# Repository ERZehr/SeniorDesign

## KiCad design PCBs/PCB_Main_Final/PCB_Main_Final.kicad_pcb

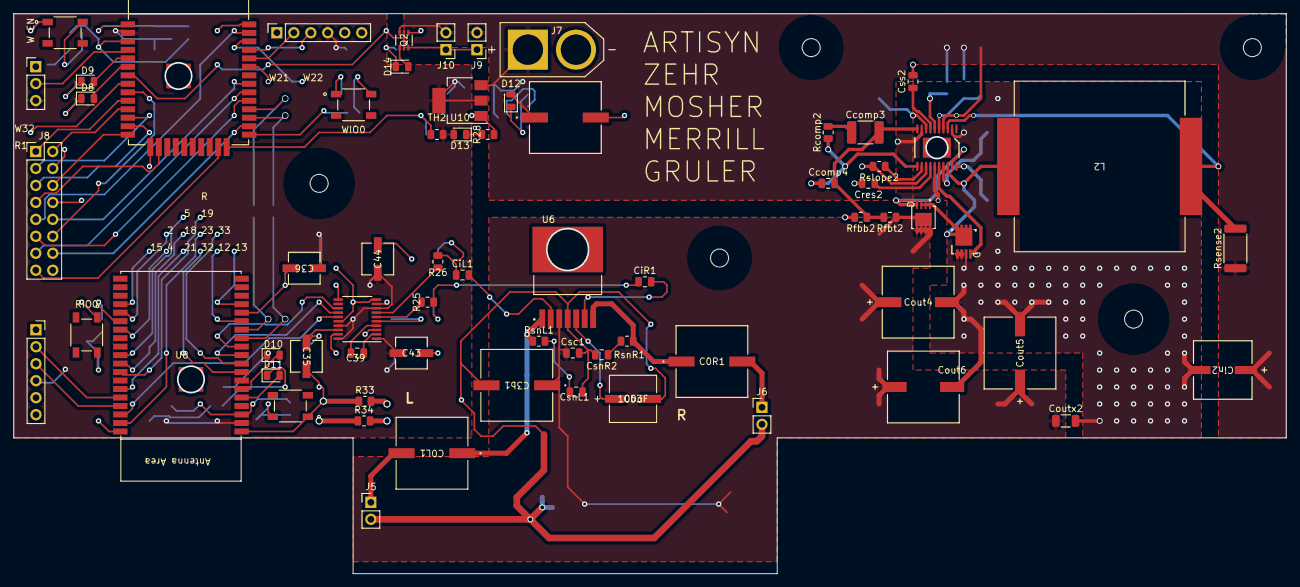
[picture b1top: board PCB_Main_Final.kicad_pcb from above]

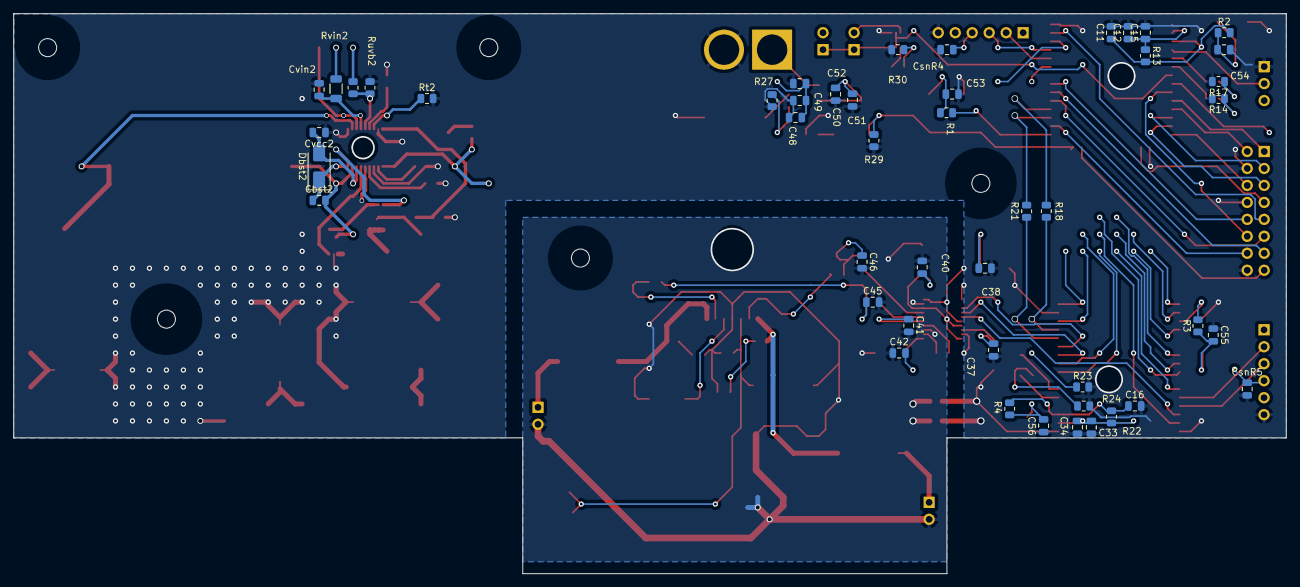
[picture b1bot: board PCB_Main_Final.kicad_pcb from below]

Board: 2 copper layers, 190.5 x 83.8 mm, 119 parts (47 on the bottom side), 85 nets.

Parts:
Boot2ROVER2, Boot2WROOM2: PinSocket_1x06_P2.54mm_Vertical
C0L1, C0R1, C3b1, C47: 1000uF; Audio_1000uF
C11, C15, C16, C34, C48, C49, C51, C53, C54, C55, C56: .1uF; C_0805_2012Metric
C12, C33: 22uF; C_0805_2012Metric
C35, C36, C43, C44: 10uF; EX_DAC_ELEC_CAPS_10uF
C37, C38, C40, C42: 0.1uF; C_0805_2012Metric
C39, C41: 2.2uF; C_0805_2012Metric
C45, C46: 2.2nF; C_0805_2012Metric
C50, C52: 10uF; C_0805_2012Metric
Cb3: 100uF; Audio_100uF
Cbst2: 470.0 nF; C_0805_2012Metric
Ccomp3: 18.0 nF; C_1812_4532Metric
Ccomp4: 1.0 nF; C_0805_2012Metric
CiL1: .1uF; C_0805_2012Metric
CiR1: .1uF; C_0805_2012Metric
Cin2: 270uF; PCAP_SVP_E7_PAN
Cout4, Cout5, Cout6: 560.0 uF; PCAP_SVP_F12_PAN
Coutx2: 47.0 uF; C_1206_3216Metric
Cres2: 470.0 nF; C_0805_2012Metric
Csc1: .1uF; C_0805_2012Metric
CsnL1: .1uF; C_0805_2012Metric
CsnR2, CsnR4, CsnR5: .1uF; C_0805_2012Metric
Css2: 33.0 nF; C_0805_2012Metric
Cvcc2: 10.0 uF; C_0805_2012Metric
Cvin2: 470.0 nF; C_0805_2012Metric
D8, D9, D10, D11: LED; LED_0805_2012Metric
D12, D13, D14: RED LED; LED_0805_2012Metric
Dbst2: D_Schottky; D_SMA
H6, H7, H8, H9, H10: MountingHole; MountingHole_2.7mm
J5: To_Speaker_L; PinHeader_1x02_P2.54mm_Vertical
J6: To_Speaker_R; PinHeader_1x02_P2.54mm_Vertical
J7: XT60-M; AMASS_XT60-M
J8: HUB75; PinHeader_2x08_P2.54mm_Vertical
J9, J10: fan connector; PinHeader_1x02_P2.54mm_Vertical
L2: 3.3 µH; IND_R3-R_EAT
LightSensorConnector2: Conn_01x03_Pin; PinHeader_1x03_P2.54mm_Vertical
M3: CSD17581Q3; CSD17309Q3
M4: CSD17581Q3A
Q2: Fan_NMOS; Fan_MOSFET
R1, R2, R3, R4: 100; R_0805_2012Metric
R13, R22, R29: 10k; R_0805_2012Metric
R14, R17, R23, R24, R28, R30: 1k; R_0805_2012Metric
R18, R21, R33, R34: 0; R_0805_2012Metric
R25, R26: 470; R_0805_2012Metric
R27: 2k; R_0805_2012Metric
RIO0: SW_Push; Boot_Switches
Rcomp2: 23.7k; R_0805_2012Metric
Rfbb2: 3.65k; R_0805_2012Metric
Rfbt2: 39.0k; R_0805_2012Metric
Rsense2: 1.5m; R_2512_6332Metric
Rslope2: 150.0k; R_0805_2012Metric
RsnL1: 2.7; R_0805_2012Metric
RsnR1: 2.7; R_0805_2012Metric
Rt2: 41.2k; R_0805_2012Metric
Ruvb2: 19.1k; R_0805_2012Metric
Ruvt2: 49.9k; R_0805_2012Metric
Rvin2: 3.01; R_1206_3216Metric
SW8: SW_Push; Boot_Switches
TH2: Thermistor; R_0805_2012Metric
U6: LM4752TS; LM4752
U7: ESP32-WROOM-E; ESP32-WROOM-32E
U8: ESP32-WROVER-E
U9: PCM5102A; TSSOP-20_4.4x6.5mm_P0.65mm
U10: AMS1117-3.3; SOT-223-3_TabPin2
U11: LM5122MH/NOPB; LM512220A_L
W EN: SW_Push; Boot_Switches
WIO0: SW_Push; Boot_Switches

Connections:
3.3V: Boot2ROVER2.4 (VCC), Boot2WROOM2.4 (VCC), C12.1, C15.1, C33.1, C34.1, C36.1, C38.2, C40.2, C42.2, C43.1, C44.1, C51.1, C52.1, CsnR4.1, CsnR5.1, D13.2 (A), LightSensorConnector2.3, R13.1, R22.1, TH2.1, U7.2 (3V3), U8.2 (3V3), U9.1 (CPVDD), U9.8 (AVDD), U9.17 (XSMT), U9.20 (DVDD), U10.2 (VO)
5V: C47.1, C48.1, C49.1, C50.1, Cin2.1, D12.2 (A), J7.P (POS), J9.2, J10.2, Q2.6 (D1), Rsense2.1, Ruvt2.1, Rvin2.1, U10.3 (VI), U11.4 (CSP)
14V: C3b1.1, Cout4.1, Cout5.1, Cout6.1, Coutx2.1, Csc1.1, M4.5 (DRAIN), M4.6 (DRAIN), M4.7 (DRAIN), M4.8 (DRAIN), M4.9 (DRAIN), Rfbt2.1, U6.3 (Vcc)
AGND: C3b1.2, C40.1, C41.2, C42.1, C43.2, C44.2, C45.2, C46.2, Cb3.2, Csc1.2, CsnL1.2, CsnR2.2, J5.2, J6.2, R33.2, R34.2, U6.4 (GND), U9.3 (CPGND), U9.9 (AGND)
A_PIN: J8.9, U7.37 (GPIO23)
B1_PIN: J8.3, U7.12 (ADC2_CH7/GPIO27)
B2_PIN: J8.7, U7.16 (MTCK/GPIO13/ADC2_CH4)
B_PIN: J8.10, U7.31 (GPIO19)
CLK_PIN: J8.13, U7.30 (GPIO18)
C_PIN: J8.11, U7.29 (GPIO5)
D_PIN: J8.12, U7.9 (32K_XN/GPIO33/ADC1_CH5)
EN_ROVER: C16.1, R4.2, R22.2, U8.3 (EN/CHIP_PU)
EN_WROOM: C11.1, R2.2, R13.2, U7.3 (EN/CHIP_PU)
G1_PIN: J8.2, U7.11 (DAC_2/ADC2_CH9/GPIO26)
G2_PIN: J8.6, U7.14 (MTDI/GPIO12/ADC2_CH5)
GND: Boot2ROVER2.6 (GND), Boot2WROOM2.6 (GND), C11.2, C12.2, C15.2, C16.2, C33.2, C34.2, C35.2, C36.2, C37.2, C38.1, C47.2, C48.2, C49.2, C50.2, C51.2, C52.2, C53.1, C54.1, C55.1, C56.1, Cin2.2, Cout4.2, Cout5.2, Cout6.2, Coutx2.2, Cres2.2, CsnR4.2, CsnR5.2, Css2.2, Cvcc2.1, Cvin2.2, J7.N (NEG), J8.4, J8.8, J8.16, LightSensorConnector2.1, M3.1 (S1), M3.2 (S2), M3.3 (S3), Q2.4 (S2), R14.2, R17.2, R23.2, R24.2, R27.2, R28.2, R29.2, R30.2, R33.1, R34.1, RIO0.1, Rfbb2.2, Rslope2.2, Rt2.2, Ruvb2.2, SW8.1, U7.1 (GND), U7.15 (GND), U7.38 (GND), U7.39 (GND_THERMAL), U8.1 (GND), U8.15 (GND), U8.38 (GND), U8.39 (GND_THERMAL), U9.10 (DEMP), U9.11 (FLT), U9.16 (FMT), U9.19 (DGND), U10.1 (GND), U11.2 (OPT), U11.9 (AGND), U11.13 (MODE), U11.15 (PGND), W EN.1, WIO0.1
I2S-BCK: U8.11 (DAC_2/ADC2_CH9/GPIO26), U9.13 (BCK)
I2S-WS: U8.36 (GPIO22), U9.15 (LRCK)
I2S_DATA: U8.10 (DAC_1/ADC2_CH8/GPIO25), U9.14 (DIN)
IO0_ROVER: R3.2, U8.25 (GPIO0/BOOT/ADC2_CH1)
IO0_WROOM: R1.2, U7.25 (GPIO0/BOOT/ADC2_CH1)
Left_Audio: C46.1, CiL1.1, R26.2
Light_Reading: LightSensorConnector2.2, U7.4 (SENSOR_VP/GPIO36/ADC1_CH0)
unnamed: C53.2, R1.1, WIO0.2
unnamed: C54.2, R2.1, W EN.2
unnamed: C55.2, R3.1, RIO0.2
unnamed: C56.2, R4.1, SW8.2
unnamed: Ccomp3.1, Rcomp2.2
unnamed: CsnL1.1, RsnL1.2
unnamed: CsnR2.1, RsnR1.2
unnamed: D8.2 (A), U7.6 (GPIO34/ADC1_CH6)
unnamed: D8.1 (K), R14.1
unnamed: D9.2 (A), U7.5 (SENSOR_VN/GPIO39/ADC1_CH3)
unnamed: D9.1 (K), R17.1
unnamed: D10.2 (A), U8.6 (GPIO34/ADC1_CH6)
unnamed: D10.1 (K), R23.1
unnamed: D11.2 (A), U8.5 (SENSOR_VN/GPIO39/ADC1_CH3)
unnamed: D11.1 (K), R24.1
unnamed: D12.1 (K), R27.1
unnamed: D13.1 (K), R28.1
unnamed: D14.2 (A), Q2.1 (S1)
unnamed: D14.1 (K), R30.1
unnamed: Cvcc2.2, Dbst2.2 (A), U11.17 (VCC)
unnamed: Cbst2.1, Dbst2.1 (K), U11.20 (BST)
unnamed: J9.1, J10.1, Q2.3 (D2)
unnamed: C0L1.2, J5.1
unnamed: C0R1.2, J6.1
unnamed: Cbst2.2, L2.2, M3.5 (D1), M3.6 (D2), M3.7 (D3), M3.8 (D4), M3.9 (Back), M4.1 (SOURCE), M4.2 (SOURCE), M4.3 (SOURCE), U11.18 (SW)
unnamed: M3.4 (G), U11.16 (LO)
unnamed: M4.4 (GATE), U11.19 (HO)
unnamed: C39.2, U9.4 (CAPM)
unnamed: C39.1, U9.2 (CAPP)
unnamed: C35.1, C37.1, U9.18 (LDOO)
unnamed: R25.1, U9.6 (OUTL)
unnamed: R26.1, U9.7 (OUTR)
unnamed: C41.1, U9.5 (VNEG)
unnamed: Ccomp4.1, Rcomp2.1, U11.11 (COMP)
unnamed: L2.1, Rsense2.2, U11.3 (CSN)
unnamed: Ccomp3.2, Ccomp4.2, Rfbb2.1, Rfbt2.2, U11.10 (FB)
unnamed: Cres2.1, U11.14 (RES)
unnamed: Rslope2.1, U11.12 (SLOPE)
unnamed: Css2.1, U11.7 (SS)
unnamed: Rt2.1, U11.8 (SYNCIN_RT)
unnamed: Ruvb2.1, Ruvt2.2, U11.6 (UVLO)
unnamed: Cvin2.1, Rvin2.2, U11.5 (VIN)
unnamed: Cb3.1, U6.5 (Bias)
unnamed: CiR1.2, U6.6 (In_A)
unnamed: CiL1.2, U6.2 (In_B)
unnamed: C0R1.1, RsnR1.1, U6.7 (Out_A)
unnamed: C0L1.1, RsnL1.1, U6.1 (Out_B)
OE_PIN: J8.15, U7.23 (MTDO/GPIO15/ADC2_CH3)
R1_PIN: J8.1, U7.10 (DAC_1/ADC2_CH8/GPIO25)
R2_PIN: J8.5, U7.13 (MTMS/GPIO14/ADC2_CH6)
ROVER_TALK_RX: R18.2, U8.13 (MTMS/GPIO14/ADC2_CH6)
ROVER_TALK_TX: R21.2, U8.12 (ADC2_CH7/GPIO27)
RXD0_ROVER: Boot2ROVER2.2 (RX), U8.34 (U0RXD/GPIO3)
RXD0_WROOM: Boot2WROOM2.2 (RX), U7.34 (U0RXD/GPIO3)
Right_Audio: C45.1, CiR1.1, R25.2
STB: J8.14, U7.26 (ADC2_CH0/GPIO4)
TXD0_ROVER: Boot2ROVER2.3 (TX), U8.35 (U0TXD/GPIO1)
TXD0_WROOM: Boot2WROOM2.3 (TX), U7.35 (U0TXD/GPIO1)
Therm_Reading: R29.1, TH2.2, U7.24 (ADC2_CH2/GPIO2)
WROOM_TALK_RX: R21.1, U7.27 (GPIO16)
WROOM_TALK_TX: R18.1, U7.28 (GPIO17)
WROOM_TO_FANS: Q2.2 (G1), Q2.5 (G2), U7.7 (GPIO35/ADC1_CH7)

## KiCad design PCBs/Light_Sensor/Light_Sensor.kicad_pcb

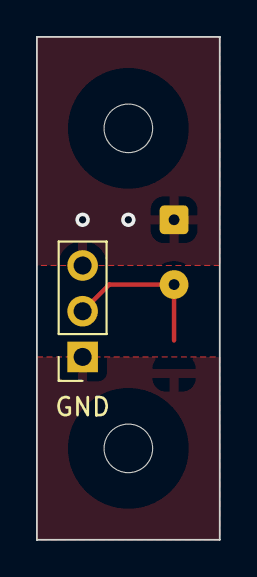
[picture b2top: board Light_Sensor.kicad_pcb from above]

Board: 2 copper layers, 10.2 x 27.9 mm, 5 parts (1 on the bottom side), 3 nets.

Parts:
D1: D_Photo; SolderWire-0.1sqmm_1x02_P3.6mm_D0.4mm_OD1mm
GND: Conn_01x03; PinSocket_1x03_P2.54mm_Vertical
H1, H2: MountingHole; MountingHole_2.7mm
R1: 10k; R_0805_2012Metric

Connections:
3.3V: D1.1 (K), GND.3
GND: GND.1, R1.2
unnamed: D1.2 (A), GND.2, R1.1

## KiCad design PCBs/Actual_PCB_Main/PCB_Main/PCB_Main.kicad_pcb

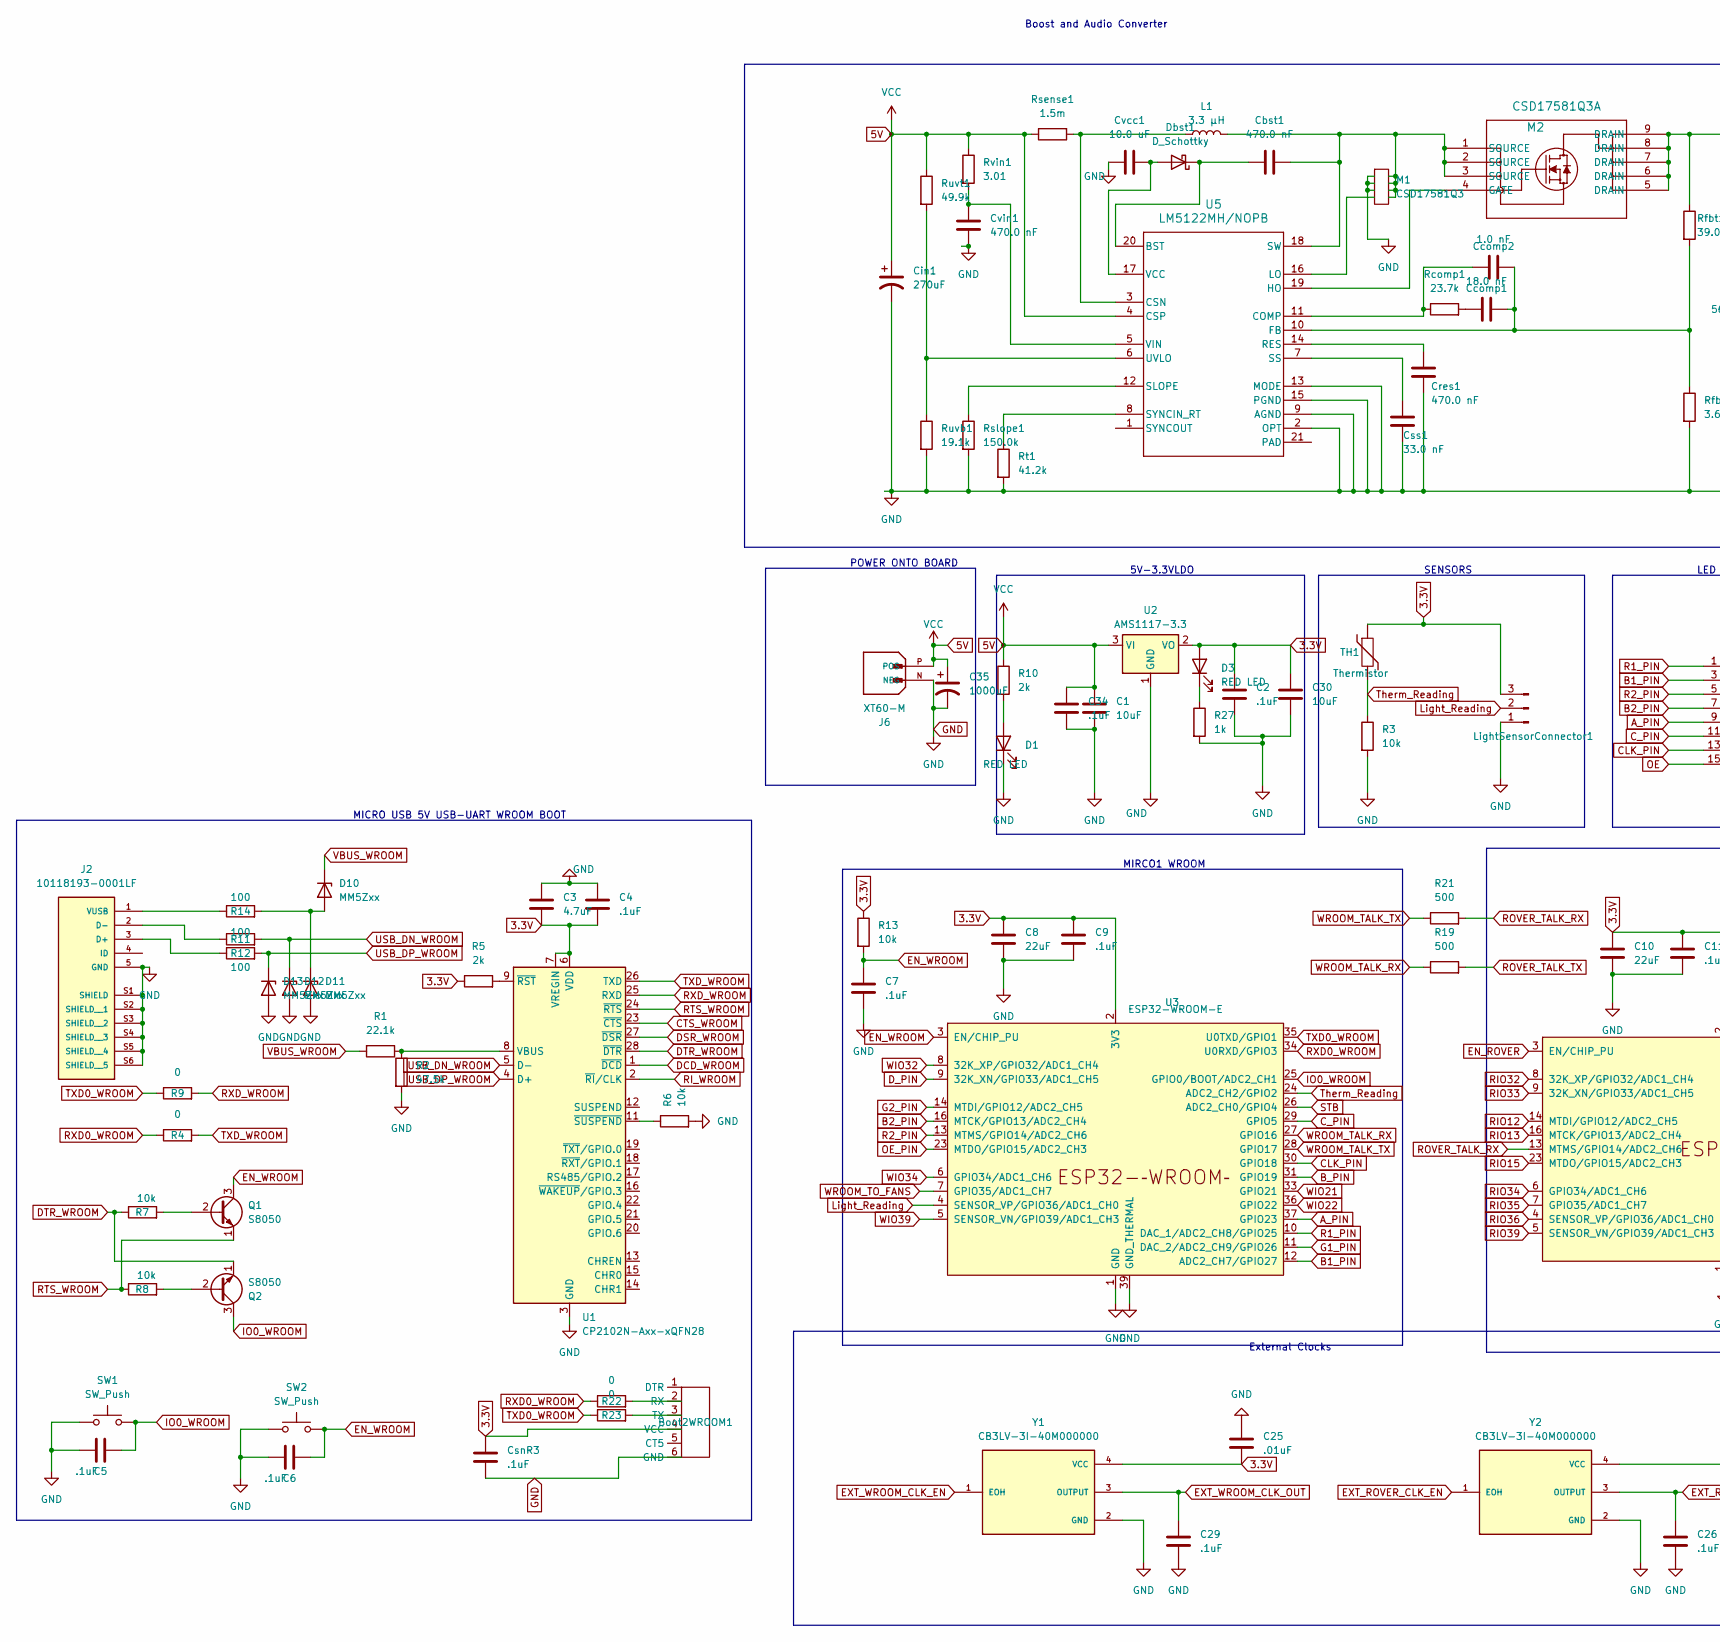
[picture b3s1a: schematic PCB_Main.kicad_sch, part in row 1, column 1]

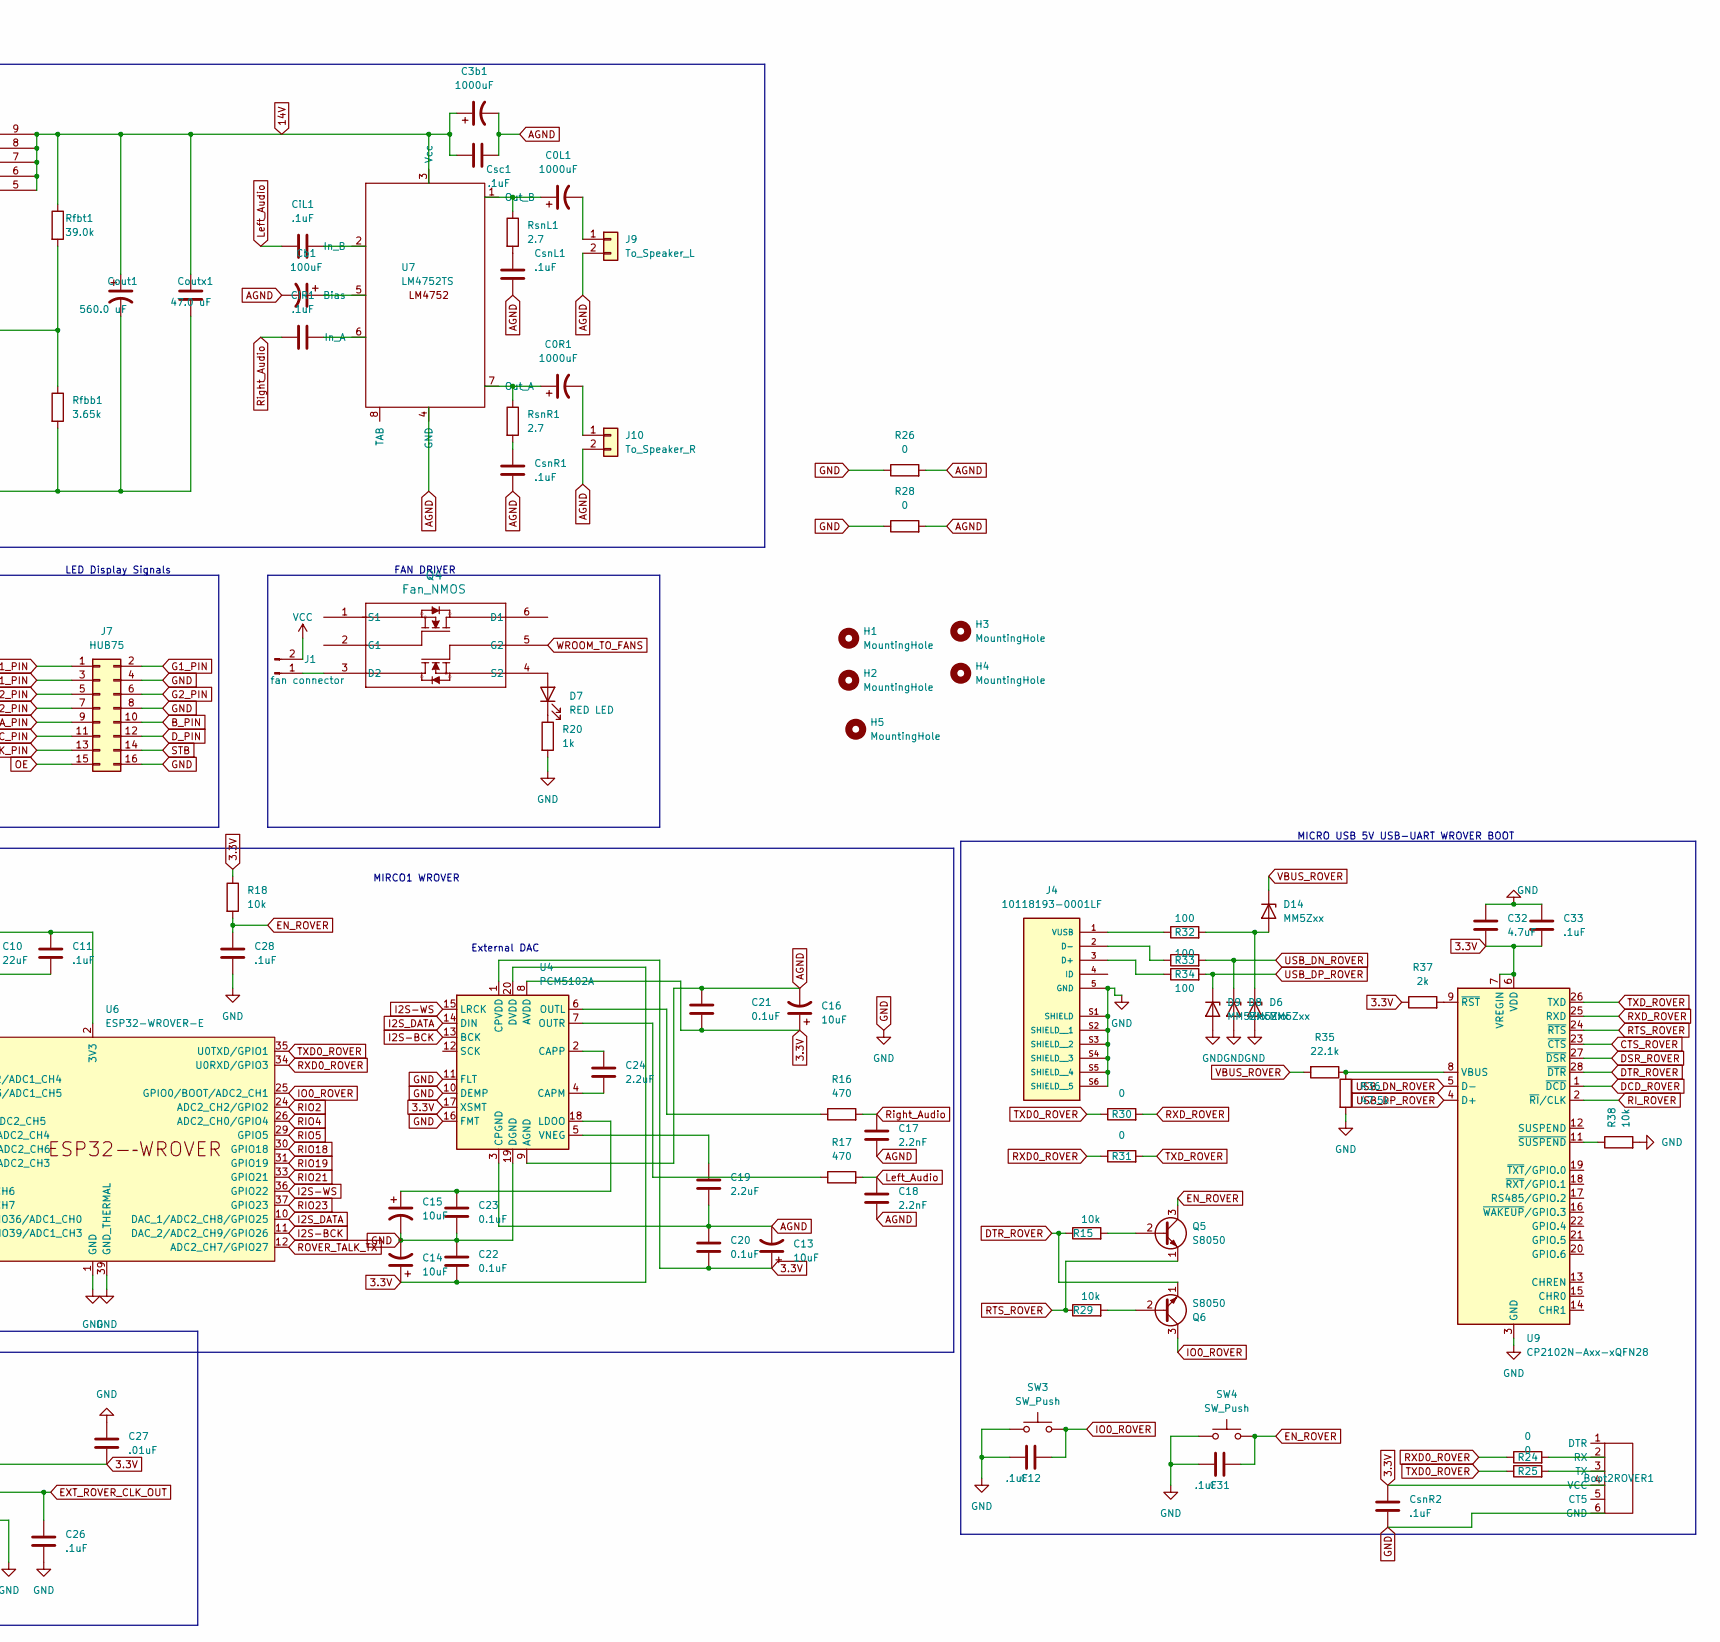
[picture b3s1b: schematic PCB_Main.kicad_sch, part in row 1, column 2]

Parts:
Boot2ROVER1, Boot2WROOM1: USB_TO_TTL_FT232RL
C0L1, C0R1, C3b1, C35: 1000uF; Audio_1000uF
C1, C30: 10uF; C_0805_2012Metric
C2, C4, C5, C6, C7, C9, C11, C12, C26, C28, C29, C31, C33, C34: .1uF; C_0805_2012Metric
C3, C32: 4.7uF; C_0805_2012Metric
C8, C10: 22uF; C_0805_2012Metric
C13, C14, C15, C16: 10uF; EX_DAC_ELEC_CAPS_10uF
C17, C18: 2.2nF; C_0805_2012Metric
C19, C24: 2.2uF; C_0805_2012Metric
C20, C21, C22, C23: 0.1uF; C_0805_2012Metric
C25, C27: .01uF; C_0805_2012Metric
Cb1: 100uF; Audio_100uF
Cbst1: 470.0 nF; C_0805_2012Metric
Ccomp1: 18.0 nF; C_1812_4532Metric
Ccomp2: 1.0 nF; C_0805_2012Metric
CiL1: .1uF; C_0805_2012Metric
CiR1: .1uF; C_0805_2012Metric
Cin1: 270uF; PCAP_SVP_E7_PAN
Cout1: 560.0 uF; PCAP_SVP_F12_PAN
Coutx1: 47.0 uF; C_1206_3216Metric
Cres1: 470.0 nF; C_0805_2012Metric
Csc1: .1uF; C_0805_2012Metric
CsnL1: .1uF; C_0805_2012Metric
CsnR1, CsnR2, CsnR3: .1uF; C_0805_2012Metric
Css1: 33.0 nF; C_0805_2012Metric
Cvcc1: 10.0 uF; C_0805_2012Metric
Cvin1: 470.0 nF; C_0805_2012Metric
D1, D3, D7: RED LED; LED_0805_2012Metric
D6, D8, D9, D10, D11, D12, D13, D14: MM5Zxx; D_SOD-523
Dbst1: D_Schottky; D_SMA
H1, H2, H3, H4, H5: MountingHole; MountingHole_2.7mm
J1: fan connector; PinHeader_1x02_P2.54mm_Vertical
J2, J4: 10118193-0001LF; Artysin_USB_CONN; PARTREV E
J6: XT60-M; AMASS_XT60-M; PARTREV V1.2
J7: HUB75; PinHeader_2x08_P2.54mm_Vertical
J9: To_Speaker_L; PinHeader_1x02_P2.54mm_Vertical
J10: To_Speaker_R; PinHeader_1x02_P2.54mm_Vertical
L1: 3.3 µH; IND_R3-R_EAT
LightSensorConnector1: Conn_01x03_Pin; PinHeader_1x03_P2.54mm_Vertical
M1: CSD17581Q3; CSD17309Q3
M2: CSD17581Q3A
Q1, Q2, Q5, Q6: S8050; TO-92_Inline
Q4: Fan_NMOS; Fan_MOSFET
R1, R35: 22.1k; R_0805_2012Metric
R2, R36: 47.5k; R_0805_2012Metric
R3, R6, R7, R8, R13, R15, R18, R29, R38: 10k; R_0805_2012Metric
R4, R9, R22, R23, R24, R25, R26, R28, R30, R31: 0; R_0805_2012Metric
R5, R10, R37: 2k; R_0805_2012Metric
R11, R12, R14, R32, R33, R34: 100; R_0805_2012Metric
R16, R17: 470; R_0805_2012Metric
R19, R21: 500; R_0805_2012Metric
R20, R27: 1k; R_0805_2012Metric
Rcomp1: 23.7k; R_0805_2012Metric
Rfbb1: 3.65k; R_0805_2012Metric
Rfbt1: 39.0k; R_0805_2012Metric
Rsense1: 1.5m; R_2512_6332Metric
Rslope1: 150.0k; R_0805_2012Metric
RsnL1: 2.7; R_0805_2012Metric
RsnR1: 2.7; R_0805_2012Metric
Rt1: 41.2k; R_0805_2012Metric
Ruvb1: 19.1k; R_0805_2012Metric
Ruvt1: 49.9k; R_0805_2012Metric
Rvin1: 3.01; R_1206_3216Metric
SW1, SW2, SW3, SW4: SW_Push; Boot_Switches
TH1: Thermistor; R_0805_2012Metric
U1, U9: CP2102N-Axx-xQFN28; QFN-28-1EP_5x5mm_P0.5mm_EP3.35x3.35mm
U2: AMS1117-3.3; SOT-223-3_TabPin2
U3: ESP32-WROOM-E; ESP32-WROOM-32E
U4: PCM5102A; TSSOP-20_4.4x6.5mm_P0.65mm
U5: LM5122MH/NOPB; LM512220A_L
U6: ESP32-WROVER-E
U7: LM4752TS; LM4752
Y1, Y2: CB3LV-3I-40M000000; Onboard_Clock; PARTREV NA

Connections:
3.3V: Boot2ROVER1.4 (VCC), Boot2WROOM1.4 (VCC), C2.1, C3.2, C4.2, C8.1, C9.1, C10.1, C11.1, C13.1, C14.1, C16.1, C20.2, C21.2, C22.2, C25.2, C27.2, C30.1, C32.2, C33.2, CsnR2.1, CsnR3.1, D3.2 (A), LightSensorConnector1.3, R5.1, R13.1, R18.1, R37.1, TH1.1, U1.6 (VDD), U1.7 (VREGIN), U2.2 (VO), U3.2 (3V3), U4.1 (CPVDD), U4.8 (AVDD), U4.17 (XSMT), U4.20 (DVDD), U6.2 (3V3), U9.6 (VDD), U9.7 (VREGIN), Y1.4 (VCC), Y2.4 (VCC); also elsewhere on the board
5V: C1.1, C34.1, C35.1, Cin1.1, J1.2, J6.P (POS), R10.1, Rsense1.1, Ruvt1.1, Rvin1.1, U2.3 (VI), U5.4 (CSP)
14V: C3b1.1, Cout1.1, Coutx1.1, Csc1.1, M2.5 (DRAIN), M2.6 (DRAIN), M2.7 (DRAIN), M2.8 (DRAIN), M2.9 (DRAIN), Rfbt1.1, U7.3 (Vcc); also elsewhere on the board
AGND: C3b1.2, C13.2, C16.2, C17.2, C18.2, C19.2, C20.1, C21.1, Cb1.2, Csc1.2, CsnL1.2, CsnR1.2, J9.2, J10.2, R26.2, R28.2, U4.3 (CPGND), U4.9 (AGND), U7.4 (GND)
A_PIN: J7.9, U3.37 (GPIO23)
B1_PIN: J7.3, U3.12 (ADC2_CH7/GPIO27)
B2_PIN: J7.7, U3.16 (MTCK/GPIO13/ADC2_CH4)
B_PIN: J7.10, U3.31 (GPIO19)
CLK_PIN: J7.13, U3.30 (GPIO18)
CTS_ROVER: U9.23 (~CTS)
CTS_WROOM: U1.23 (~CTS)
C_PIN: J7.11, U3.29 (GPIO5)
DCD_ROVER: U9.1 (~DCD)
DCD_WROOM: U1.1 (~DCD)
DSR_ROVER: U9.27 (~DSR)
DSR_WROOM: U1.27 (~DSR)
DTR_ROVER: Q6.1 (E), R15.1, U9.28 (~DTR)
DTR_WROOM: Q2.1 (E), R7.1, U1.28 (~DTR)
D_PIN: J7.12, U3.9 (32K_XN/GPIO33/ADC1_CH5)
EN_ROVER: C28.1, C31.2, Q5.3 (C), R18.2, SW4.2, U6.3 (EN/CHIP_PU)
EN_WROOM: C6.2, C7.1, Q1.3 (C), R13.2, SW2.2, U3.3 (EN/CHIP_PU)
EXT_ROVER_CLK_EN: Y2.1 (EOH)
EXT_ROVER_CLK_OUT: C26.1, Y2.3 (OUTPUT)
EXT_WROOM_CLK_EN: Y1.1 (EOH)
EXT_WROOM_CLK_OUT: C29.1, Y1.3 (OUTPUT)
G1_PIN: J7.2, U3.11 (DAC_2/ADC2_CH9/GPIO26)
G2_PIN: J7.6, U3.14 (MTDI/GPIO12/ADC2_CH5)
GND: Boot2ROVER1.6 (GND), Boot2WROOM1.6 (GND), C1.2, C2.2, C3.1, C4.1, C5.1, C6.1, C7.2, C8.2, C9.2, C10.2, C11.2, C12.1, C14.2, C15.2, C22.1, C23.2, C25.1, C26.2, C27.1, C28.2, C29.2, C30.2, C31.1, C32.1, C33.1, C34.2, C35.2, Cin1.2, Cout1.2, Coutx1.2, Cres1.2, CsnR2.2, CsnR3.2, Css1.2, Cvcc1.1, Cvin1.2, D1.1 (K), D6.2 (A), D8.2 (A), D9.2 (A), D11.2 (A), D12.2 (A), D13.2 (A), J2.5 (GND), J2.S1 (SHIELD), J2.S2 (SHIELD__1), J2.S3 (SHIELD__2), J2.S4 (SHIELD__3), J2.S5 (SHIELD__4), J2.S6 (SHIELD__5), J4.5 (GND), J4.S1 (SHIELD), J4.S2 (SHIELD__1), J4.S3 (SHIELD__2), J4.S4 (SHIELD__3), J4.S5 (SHIELD__4), J4.S6 (SHIELD__5), J6.N (NEG), J7.4, J7.8, J7.16, LightSensorConnector1.1, M1.1 (S1), M1.2 (S2), M1.3 (S3), R2.2, R3.2, R6.2, R20.2, R26.1, R27.2, R28.1, R36.2, R38.2, Rfbb1.2, Rslope1.2, Rt1.2, Ruvb1.2, SW1.1, SW2.1, SW3.1, SW4.1, U1.3 (GND), U1.29 (GND), U2.1 (GND), U3.1 (GND), U3.15 (GND), U3.38 (GND), U3.39 (GND_THERMAL), U4.10 (DEMP), U4.11 (FLT), U4.16 (FMT), U4.19 (DGND), U5.2 (OPT), U5.9 (AGND), U5.13 (MODE), U5.15 (PGND), U6.1 (GND), U6.15 (GND), U6.38 (GND), U6.39 (GND_THERMAL), U9.3 (GND), U9.29 (GND), Y1.2 (GND), Y2.2 (GND); also elsewhere on the board
I2S-BCK: U4.13 (BCK), U6.11 (DAC_2/ADC2_CH9/GPIO26)
I2S-WS: U4.15 (LRCK), U6.36 (GPIO22)
I2S_DATA: U4.14 (DIN), U6.10 (DAC_1/ADC2_CH8/GPIO25)
IO0_ROVER: C12.2, Q6.3 (C), SW3.2, U6.25 (GPIO0/BOOT/ADC2_CH1)
IO0_WROOM: C5.2, Q2.3 (C), SW1.2, U3.25 (GPIO0/BOOT/ADC2_CH1)
Left_Audio: C18.1, CiL1.1, R17.2
Light_Reading: LightSensorConnector1.2, U3.4 (SENSOR_VP/GPIO36/ADC1_CH0); also elsewhere on the board
unnamed: Boot2ROVER1.2 (RX), R24.2
unnamed: Boot2ROVER1.3 (TX), R25.2
unnamed 37: Boot2WROOM1.2 (RX), R22.2; also elsewhere on the board
unnamed 38: Boot2WROOM1.3 (TX), R23.2; also elsewhere on the board
unnamed: Ccomp1.1, Rcomp1.2
unnamed: CsnL1.1, RsnL1.2
unnamed: CsnR1.1, RsnR1.2
unnamed: D1.2 (A), R10.2
unnamed: D3.1 (K), R27.1
unnamed: D7.2 (A), Q4.4 (S2)
unnamed: D7.1 (K), R20.1
unnamed: D10.2 (A), D11.1 (K), R14.2
unnamed: D6.1 (K), D14.2 (A), R32.2
unnamed: Cvcc1.2, Dbst1.2 (A), U5.17 (VCC)
unnamed: Cbst1.1, Dbst1.1 (K), U5.20 (BST)
unnamed: J1.1, Q4.3 (D2)
unnamed: J2.3 (D+), R12.1
unnamed: J2.2 (D-), R11.1
unnamed: J2.1 (VUSB), R14.1
unnamed: J4.3 (D+), R34.1
unnamed: J4.2 (D-), R33.1
unnamed: J4.1 (VUSB), R32.1
unnamed: C0L1.2, J9.1
unnamed: C0R1.2, J10.1
unnamed: Cbst1.2, L1.2, M1.5 (D1), M1.6 (D2), M1.7 (D3), M1.8 (D4), M2.1 (SOURCE), M2.2 (SOURCE), M2.3 (SOURCE), U5.18 (SW)
unnamed: M1.4 (G), U5.16 (LO)
unnamed: M2.4 (GATE), U5.19 (HO)
unnamed: Q1.2 (B), R7.2
unnamed: Q2.2 (B), R8.2
unnamed: Q5.2 (B), R15.2
unnamed: Q6.2 (B), R29.2
unnamed: R1.1, R2.1, U1.8 (VBUS)
unnamed: R5.2, U1.9 (~RST)
unnamed: R6.1, U1.11 (~SUSPEND)
unnamed: C24.2, U4.4 (CAPM)
unnamed: C24.1, U4.2 (CAPP)
unnamed: C15.1, C23.1, U4.18 (LDOO)
unnamed: R16.1, U4.6 (OUTL)
unnamed: R17.1, U4.7 (OUTR)
unnamed: C19.1, U4.5 (VNEG)
unnamed: Ccomp2.1, Rcomp1.1, U5.11 (COMP)
unnamed: L1.1, Rsense1.2, U5.3 (CSN)
unnamed: Ccomp1.2, Ccomp2.2, Rfbb1.1, Rfbt1.2, U5.10 (FB)
unnamed: Cres1.1, U5.14 (RES)
unnamed: Rslope1.1, U5.12 (SLOPE)
unnamed: Css1.1, U5.7 (SS)
unnamed: Rt1.1, U5.8 (SYNCIN_RT)
unnamed: Ruvb1.1, Ruvt1.2, U5.6 (UVLO)
unnamed: Cvin1.1, Rvin1.2, U5.5 (VIN)
unnamed: Cb1.1, U7.5 (Bias)
unnamed: CiR1.2, U7.6 (In_A)
unnamed: CiL1.2, U7.2 (In_B)
unnamed: C0R1.1, RsnR1.1, U7.7 (Out_A)
unnamed: C0L1.1, RsnL1.1, U7.1 (Out_B)
unnamed: R35.1, R36.1, U9.8 (VBUS)
unnamed: R37.2, U9.9 (~RST)
unnamed: R38.1, U9.11 (~SUSPEND)
OE: J7.15
OE_PIN: U3.23 (MTDO/GPIO15/ADC2_CH3)
R1_PIN: J7.1, U3.10 (DAC_1/ADC2_CH8/GPIO25)
R2_PIN: J7.5, U3.13 (MTMS/GPIO14/ADC2_CH6)
RIO2: U6.24 (ADC2_CH2/GPIO2)
RIO4: U6.26 (ADC2_CH0/GPIO4)
RIO5: U6.29 (GPIO5)
RIO12: U6.14 (MTDI/GPIO12/ADC2_CH5)
RIO13: U6.16 (MTCK/GPIO13/ADC2_CH4)
RIO15: U6.23 (MTDO/GPIO15/ADC2_CH3)
RIO18: U6.30 (GPIO18)
RIO19: U6.31 (GPIO19)
RIO21: U6.33 (GPIO21)
RIO23: U6.37 (GPIO23)
RIO32: U6.8 (32K_XP/GPIO32/ADC1_CH4)
RIO33: U6.9 (32K_XN/GPIO33/ADC1_CH5)
RIO34: U6.6 (GPIO34/ADC1_CH6)
RIO35: U6.7 (GPIO35/ADC1_CH7)
RIO36: U6.4 (SENSOR_VP/GPIO36/ADC1_CH0)
RIO39: U6.5 (SENSOR_VN/GPIO39/ADC1_CH3)
RI_ROVER: U9.2 (~RI/CLK)
RI_WROOM: U1.2 (~RI/CLK)
ROVER_TALK_RX: R21.2, U6.13 (MTMS/GPIO14/ADC2_CH6)
ROVER_TALK_TX: R19.2, U6.12 (ADC2_CH7/GPIO27)
RTS_ROVER: Q5.1 (E), R29.1, U9.24 (~RTS)
RTS_WROOM: Q1.1 (E), R8.1, U1.24 (~RTS)
RXD0_ROVER: R24.1, R31.1, U6.34 (U0RXD/GPIO3)
RXD0_WROOM: R4.1, R22.1, U3.34 (U0RXD/GPIO3)
RXD_ROVER: R30.2, U9.25 (RXD)
RXD_WROOM: R9.2, U1.25 (RXD)
Right_Audio: C17.1, CiR1.1, R16.2
STB: J7.14, U3.26 (ADC2_CH0/GPIO4)
TXD0_ROVER: R25.1, R30.1, U6.35 (U0TXD/GPIO1)
TXD0_WROOM: R9.1, R23.1, U3.35 (U0TXD/GPIO1)
TXD_ROVER: R31.2, U9.26 (TXD)
TXD_WROOM: R4.2, U1.26 (TXD)
Therm_Reading: R3.1, TH1.2, U3.24 (ADC2_CH2/GPIO2)
USB_DN_ROVER: D8.1 (K), R33.2, U9.5 (D-)
USB_DN_WROOM: D12.1 (K), R11.2, U1.5 (D-)
USB_DP_ROVER: D9.1 (K), R34.2, U9.4 (D+)
USB_DP_WROOM: D13.1 (K), R12.2, U1.4 (D+)
VBUS_ROVER: D14.1 (K), R35.2
VBUS_WROOM: D10.1 (K), R1.2
WIO21: U3.33 (GPIO21)
WIO22: U3.36 (GPIO22)
WIO32: U3.8 (32K_XP/GPIO32/ADC1_CH4)
WIO34: U3.6 (GPIO34/ADC1_CH6)
WIO39: U3.5 (SENSOR_VN/GPIO39/ADC1_CH3)
WROOM_TALK_RX: R19.1, U3.27 (GPIO16)
WROOM_TALK_TX: R21.1, U3.28 (GPIO17)
WROOM_TO_FANS: Q4.5 (G2), U3.7 (GPIO35/ADC1_CH7)

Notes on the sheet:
FAN DRIVER
POWER ONTO BOARD
MICRO USB 5V USB-UART WROOM BOOT
MIRCO1 WROOM
LED Display Signals
Boost and Audio Converter
5V-3.3VLDO
SENSORS
MIRCO1 WROVER
External Clocks
External DAC
MICRO USB 5V USB-UART WROVER BOOT

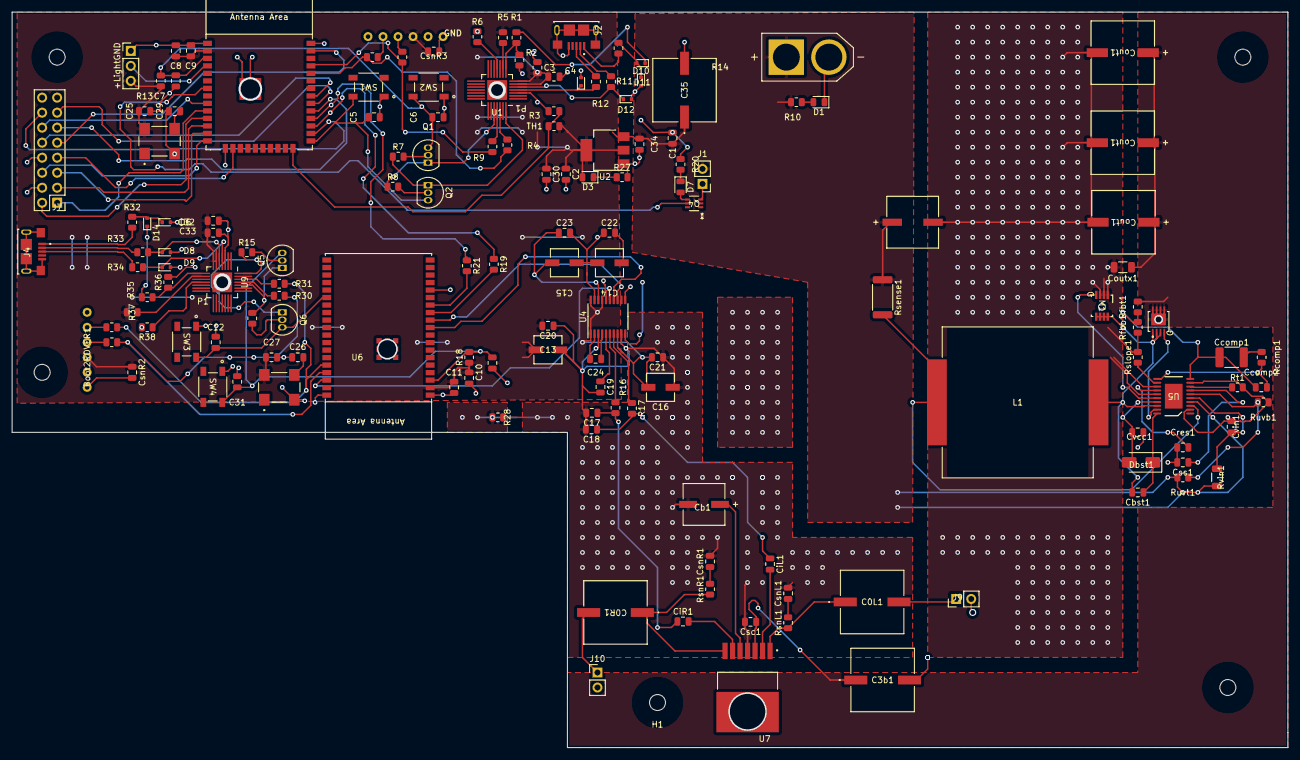
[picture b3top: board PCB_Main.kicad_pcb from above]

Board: 2 copper layers, 215.9 x 124.5 mm, 157 parts (1 on the bottom side), 110 nets.

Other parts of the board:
+LightGND: Conn_01x03_Pin; PinHeader_1x03_P2.54mm_Vertical
Cout1#2, Cout1#3: 560.0 uF; PCAP_SVP_F12_PAN
H1#2: MountingHole; MountingHole_2.7mm
WBoot2: USB_TO_TTL_FT232RL

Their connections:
3.3V: +LightGND.3, WBoot2.4 (VCC); also elsewhere on the board
14V: Cout1#2.1, Cout1#3.1; also elsewhere on the board
GND: +LightGND.1, Cout1#2.2, Cout1#3.2, WBoot2.6 (GND); also elsewhere on the board
Light_Reading: +LightGND.2; also elsewhere on the board
unnamed 37: WBoot2.2 (RX); also elsewhere on the board
unnamed 38: WBoot2.3 (TX); also elsewhere on the board

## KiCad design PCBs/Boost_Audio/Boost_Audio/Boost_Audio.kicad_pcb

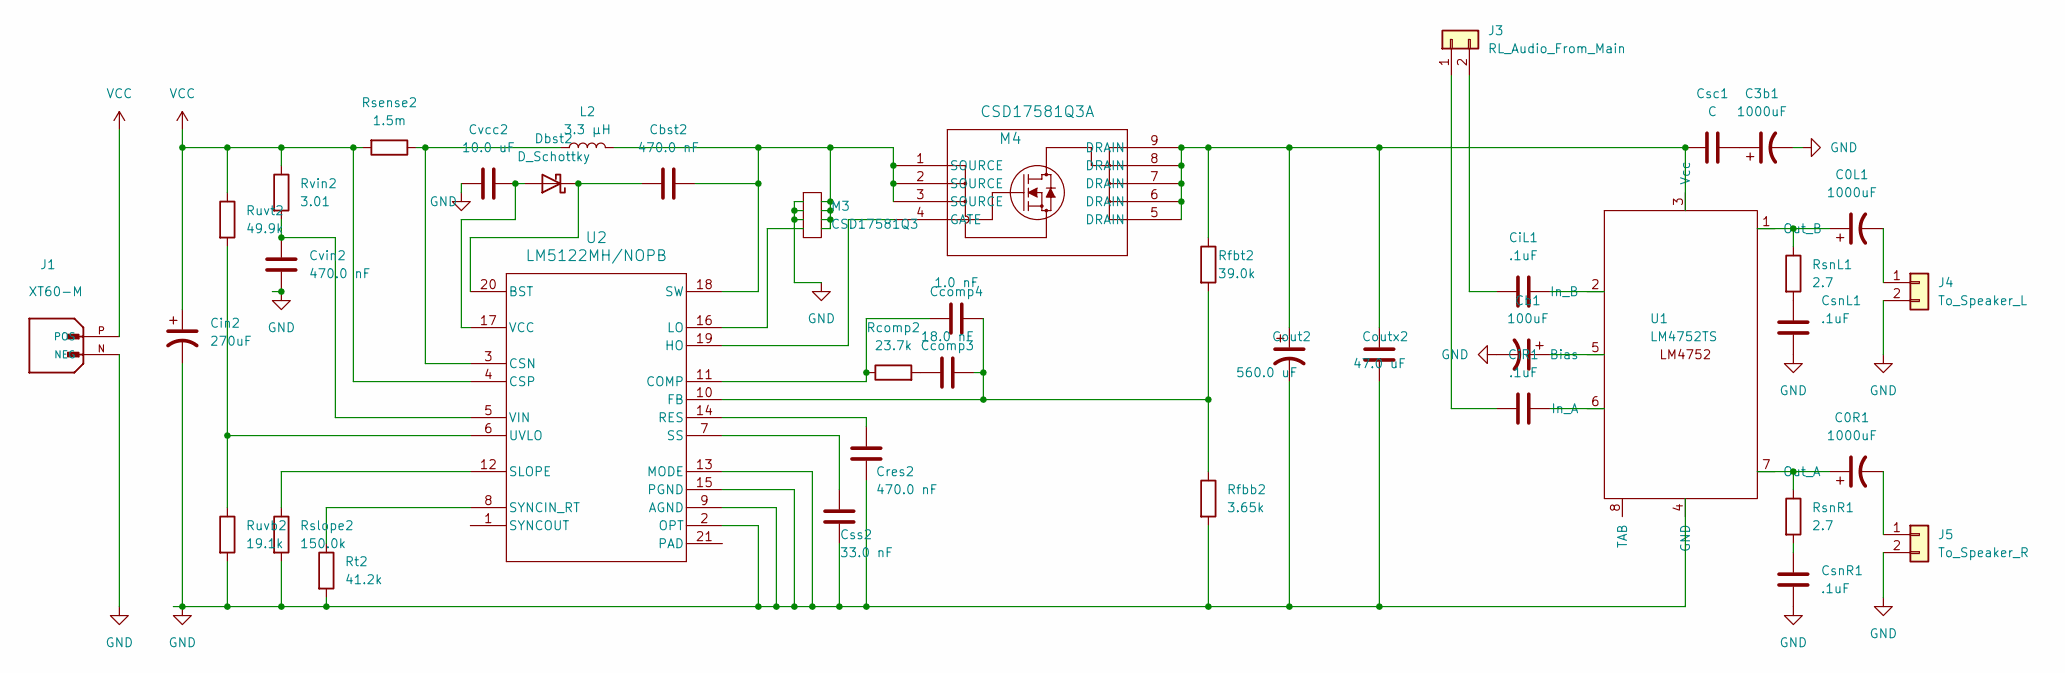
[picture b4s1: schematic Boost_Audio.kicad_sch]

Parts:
C0L1, C0R1, C3b1: 1000uF; Audio_1000uF
Cb1: 100uF; Audio_100uF
Cbst2: 470.0 nF; CSD17309Q3
Ccomp3: 18.0 nF; C_1812_4532Metric
Ccomp4: 1.0 nF; C_0805_2012Metric
CiL1: .1uF; C_0805_2012Metric
CiR1: .1uF; C_0805_2012Metric
Cin2: 270uF; PCAP_SVP_E7_PAN
Cout2: 560.0 uF; PCAP_SVP_F12_PAN
Coutx2: 47.0 uF; C_1206_3216Metric
Cres2: 470.0 nF; C_0805_2012Metric
Csc1: C; C_0805_2012Metric
CsnL1: .1uF; C_0805_2012Metric
CsnR1: .1uF; C_0805_2012Metric
Css2: 33.0 nF; C_0805_2012Metric
Cvcc2: 10.0 uF; C_0805_2012Metric
Cvin2: 470.0 nF; C_0805_2012Metric
Dbst2: D_Schottky; D_SMA
J1: XT60-M; AMASS_XT60-M; PARTREV V1.2
J3: RL_Audio_From_Main; JST_EH_B2B-EH-A_1x02_P2.50mm_Vertical
J4: To_Speaker_L; JST_EH_B2B-EH-A_1x02_P2.50mm_Vertical
J5: To_Speaker_R; JST_EH_B2B-EH-A_1x02_P2.50mm_Vertical
L2: 3.3 µH; IND_R3-R_EAT
M3: CSD17581Q3; CSD17309Q3
M4: CSD17581Q3A; CSD17309Q3A
Rcomp2: 23.7k; R_0805_2012Metric
Rfbb2: 3.65k; R_0805_2012Metric
Rfbt2: 39.0k; R_0805_2012Metric
Rsense2: 1.5m; R_2512_6332Metric
Rslope2: 150.0k; R_0805_2012Metric
RsnL1: 2.7; R_0805_2012Metric
RsnR1: 2.7; R_0805_2012Metric
Rt2: 41.2k; R_0805_2012Metric
Ruvb2: 19.1k; R_0805_2012Metric
Ruvt2: 49.9k; R_0805_2012Metric
Rvin2: 3.01; R_1206_3216Metric
U1: LM4752TS; LM4752
U2: LM5122MH/NOPB; LM512220A_L

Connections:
GND: C3b1.2, Cb1.2, Cin2.2, Cout2.2, Coutx2.2, Cres2.2, CsnL1.2, CsnR1.2, Css2.2, Cvcc2.1, Cvin2.2, J1.N (NEG), J4.2, J5.2, M3.1 (S1), M3.2 (S2), M3.3 (S3), Rfbb2.2, Rslope2.2, Rt2.2, Ruvb2.2, U1.4 (GND), U2.2 (OPT), U2.9 (AGND), U2.13 (MODE), U2.15 (PGND)
unnamed: C3b1.1, Csc1.2
unnamed: Ccomp3.1, Rcomp2.2
unnamed: CsnL1.1, RsnL1.2
unnamed: CsnR1.1, RsnR1.2
unnamed: Cvcc2.2, Dbst2.2 (A), U2.17 (VCC)
unnamed: Cbst2.1, Dbst2.1 (K), U2.20 (BST)
unnamed: CiR1.1, J3.1
unnamed: CiL1.1, J3.2
unnamed: C0L1.2, J4.1
unnamed: C0R1.2, J5.1
unnamed: Cbst2.2, L2.2, M3.5 (D1), M3.6 (D2), M3.7 (D3), M3.8 (D4), M4.1 (SOURCE), M4.2 (SOURCE), M4.3 (SOURCE), U2.18 (SW)
unnamed: M3.4 (G), U2.16 (LO)
unnamed: M4.4 (GATE), U2.19 (HO)
unnamed: Cb1.1, U1.5 (Bias)
unnamed: CiR1.2, U1.6 (In_A)
unnamed: CiL1.2, U1.2 (In_B)
unnamed: C0R1.1, RsnR1.1, U1.7 (Out_A)
unnamed: C0L1.1, RsnL1.1, U1.1 (Out_B)
unnamed: Cout2.1, Coutx2.1, Csc1.1, M4.5 (DRAIN), M4.6 (DRAIN), M4.7 (DRAIN), M4.8 (DRAIN), M4.9 (DRAIN), Rfbt2.1, U1.3 (Vcc)
unnamed: Ccomp4.1, Rcomp2.1, U2.11 (COMP)
unnamed: L2.1, Rsense2.1, U2.3 (CSN)
unnamed: Ccomp3.2, Ccomp4.2, Rfbb2.1, Rfbt2.2, U2.10 (FB)
unnamed: Cres2.1, U2.14 (RES)
unnamed: Rslope2.1, U2.12 (SLOPE)
unnamed: Css2.1, U2.7 (SS)
unnamed: Rt2.1, U2.8 (SYNCIN_RT)
unnamed: Ruvb2.1, Ruvt2.2, U2.6 (UVLO)
unnamed: Cvin2.1, Rvin2.2, U2.5 (VIN)
VCC: Cin2.1, J1.P (POS), Rsense2.2, Ruvt2.1, Rvin2.1, U2.4 (CSP)

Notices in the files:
parts and their libraries:
Copyright 2016 Accelerated Designs. All rights reserved.
